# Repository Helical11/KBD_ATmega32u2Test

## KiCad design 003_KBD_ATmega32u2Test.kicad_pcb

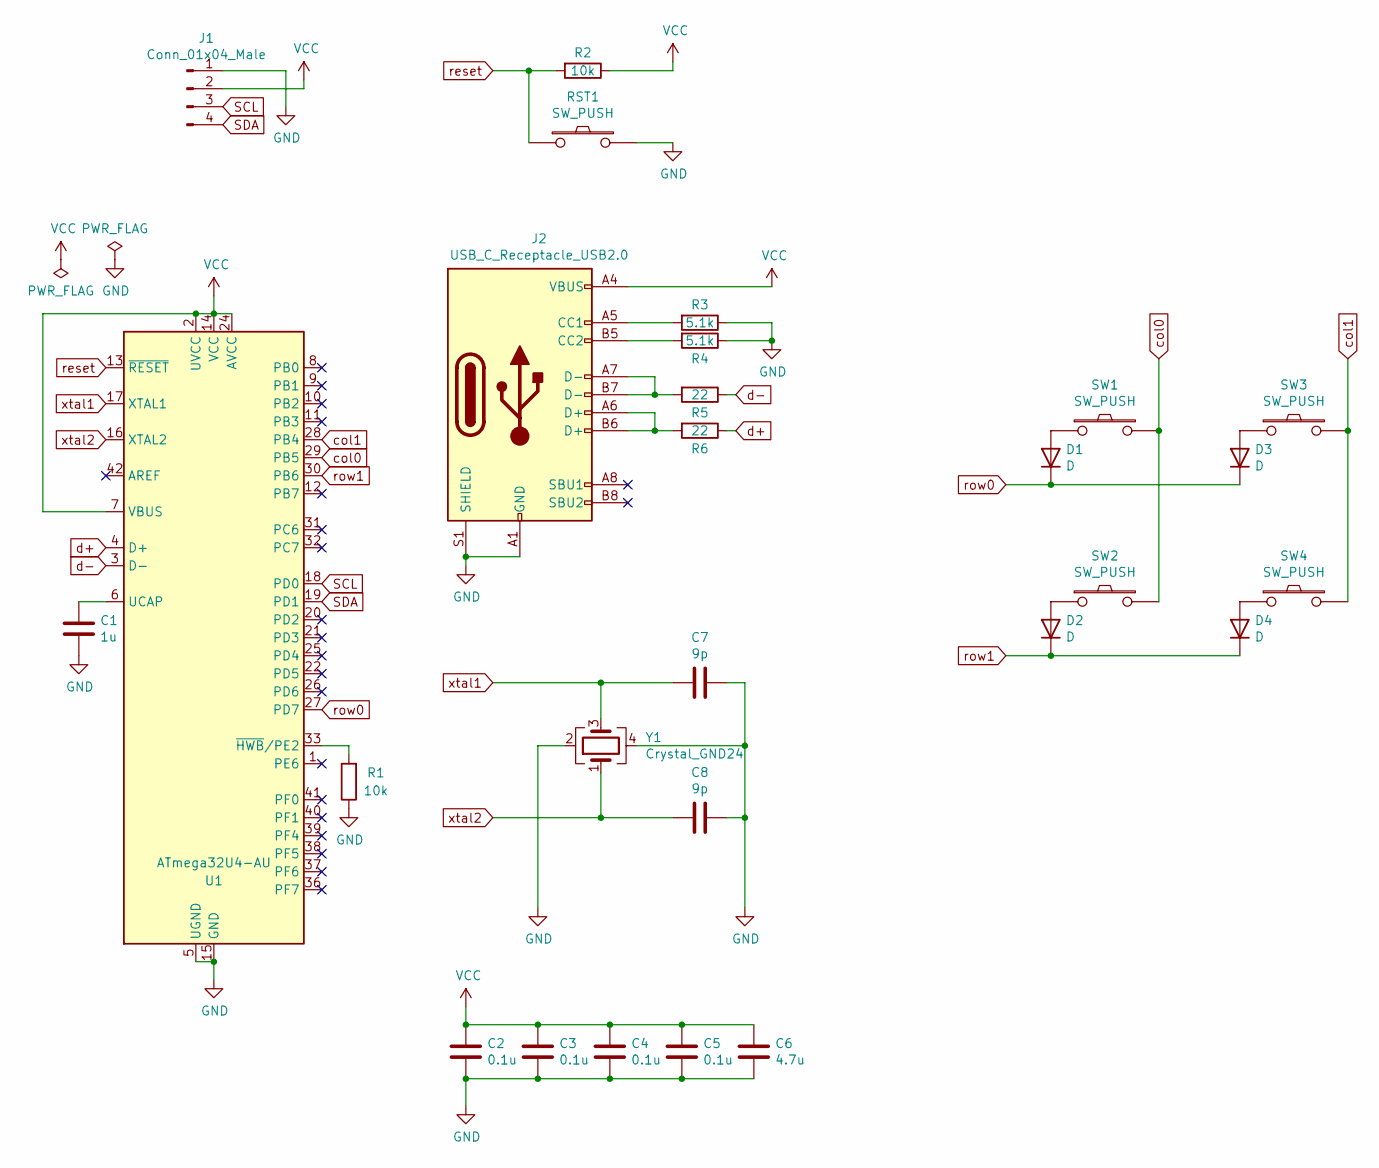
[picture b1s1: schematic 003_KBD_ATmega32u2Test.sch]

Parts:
C1: 1u; CP_EIA-1608-08_AVX-J
C2, C3, C4, C5: 0.1u; CP_EIA-1608-08_AVX-J
C6: 4.7u; CP_EIA-1608-08_AVX-J
C7, C8: 9p; CP_EIA-1608-08_AVX-J
D1, D2, D3, D4: D; D_SOD-123
J1: Conn_01x04_Male; PinSocket_1x04_P2.54mm_Vertical
J2: USB_C_Receptacle_USB2.0; USB_C_Receptacle_HRO_TYPE-C-31-M-12
R1, R2: 10k; R_0603_1608Metric
R3, R4: 5.1k; R_0603_1608Metric
R5, R6: 22; R_0603_1608Metric
RST1: SW_PUSH; ResetSW_1side
SW1, SW2, SW3, SW4: SW_PUSH; CherryMX_Hotswap
U1: ATmega32U4-AU; TQFP-44_10x10mm_P0.8mm
Y1: Crystal_GND24; Crystal_SMD_3225-4Pin_3.2x2.5mm

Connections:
GND: C1.1, C2.1, C3.1, C4.1, C5.1, C6.1, C7.1, C8.1, J1.1, J2.A1 (GND), J2.A12 (GND), J2.B1 (GND), J2.B12 (GND), J2.S1 (SHIELD), R1.1, R3.1, R4.1, RST1.2, U1.5 (UGND), U1.15 (GND), U1.23 (GND), U1.35 (GND), U1.43 (GND), Y1.2, Y1.4
unnamed: C1.2, U1.6 (UCAP)
unnamed: D1.2 (A), SW1.1
unnamed: D2.2 (A), SW2.1
unnamed: D3.2 (A), SW3.1
unnamed: D4.2 (A), SW4.1
unnamed: J2.A5 (CC1), R3.2
unnamed: J2.A6 (D+), J2.B6 (D+), R6.2
unnamed: J2.A7 (D-), J2.B7 (D-), R5.2
unnamed: J2.B5 (CC2), R4.2
unnamed: R1.2, U1.33 (~HWB~/PE2)
SCL: J1.3, U1.18 (PD0)
SDA: J1.4, U1.19 (PD1)
VCC: C2.2, C3.2, C4.2, C5.2, C6.2, J1.2, J2.A4 (VBUS), J2.A9 (VBUS), J2.B4 (VBUS), J2.B9 (VBUS), R2.1, U1.2 (UVCC), U1.7 (VBUS), U1.14 (VCC), U1.24 (AVCC), U1.34 (VCC), U1.44 (AVCC)
col0: SW1.2, SW2.2, U1.29 (PB5)
col1: SW3.2, SW4.2, U1.28 (PB4)
d+: R6.1, U1.4 (D+)
d-: R5.1, U1.3 (D-)
reset: R2.2, RST1.1, U1.13 (~RESET)
row0: D1.1 (K), D3.1 (K), U1.27 (PD7)
row1: D2.1 (K), D4.1 (K), U1.30 (PB6)
xtal1: C7.2, U1.17 (XTAL1), Y1.3
xtal2: C8.2, U1.16 (XTAL2), Y1.1

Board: 2 copper layers, 27 parts (0 on the bottom side), 23 nets, no tracks yet.

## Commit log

2022-02-06 1st commit
2022-02-06 Add Files
2022-02-06 Create LICENSE
2022-02-06 .gitignore is now working
2022-03-09 回路図の更新(ATMEGA32U4へ変更、OLED追加)
